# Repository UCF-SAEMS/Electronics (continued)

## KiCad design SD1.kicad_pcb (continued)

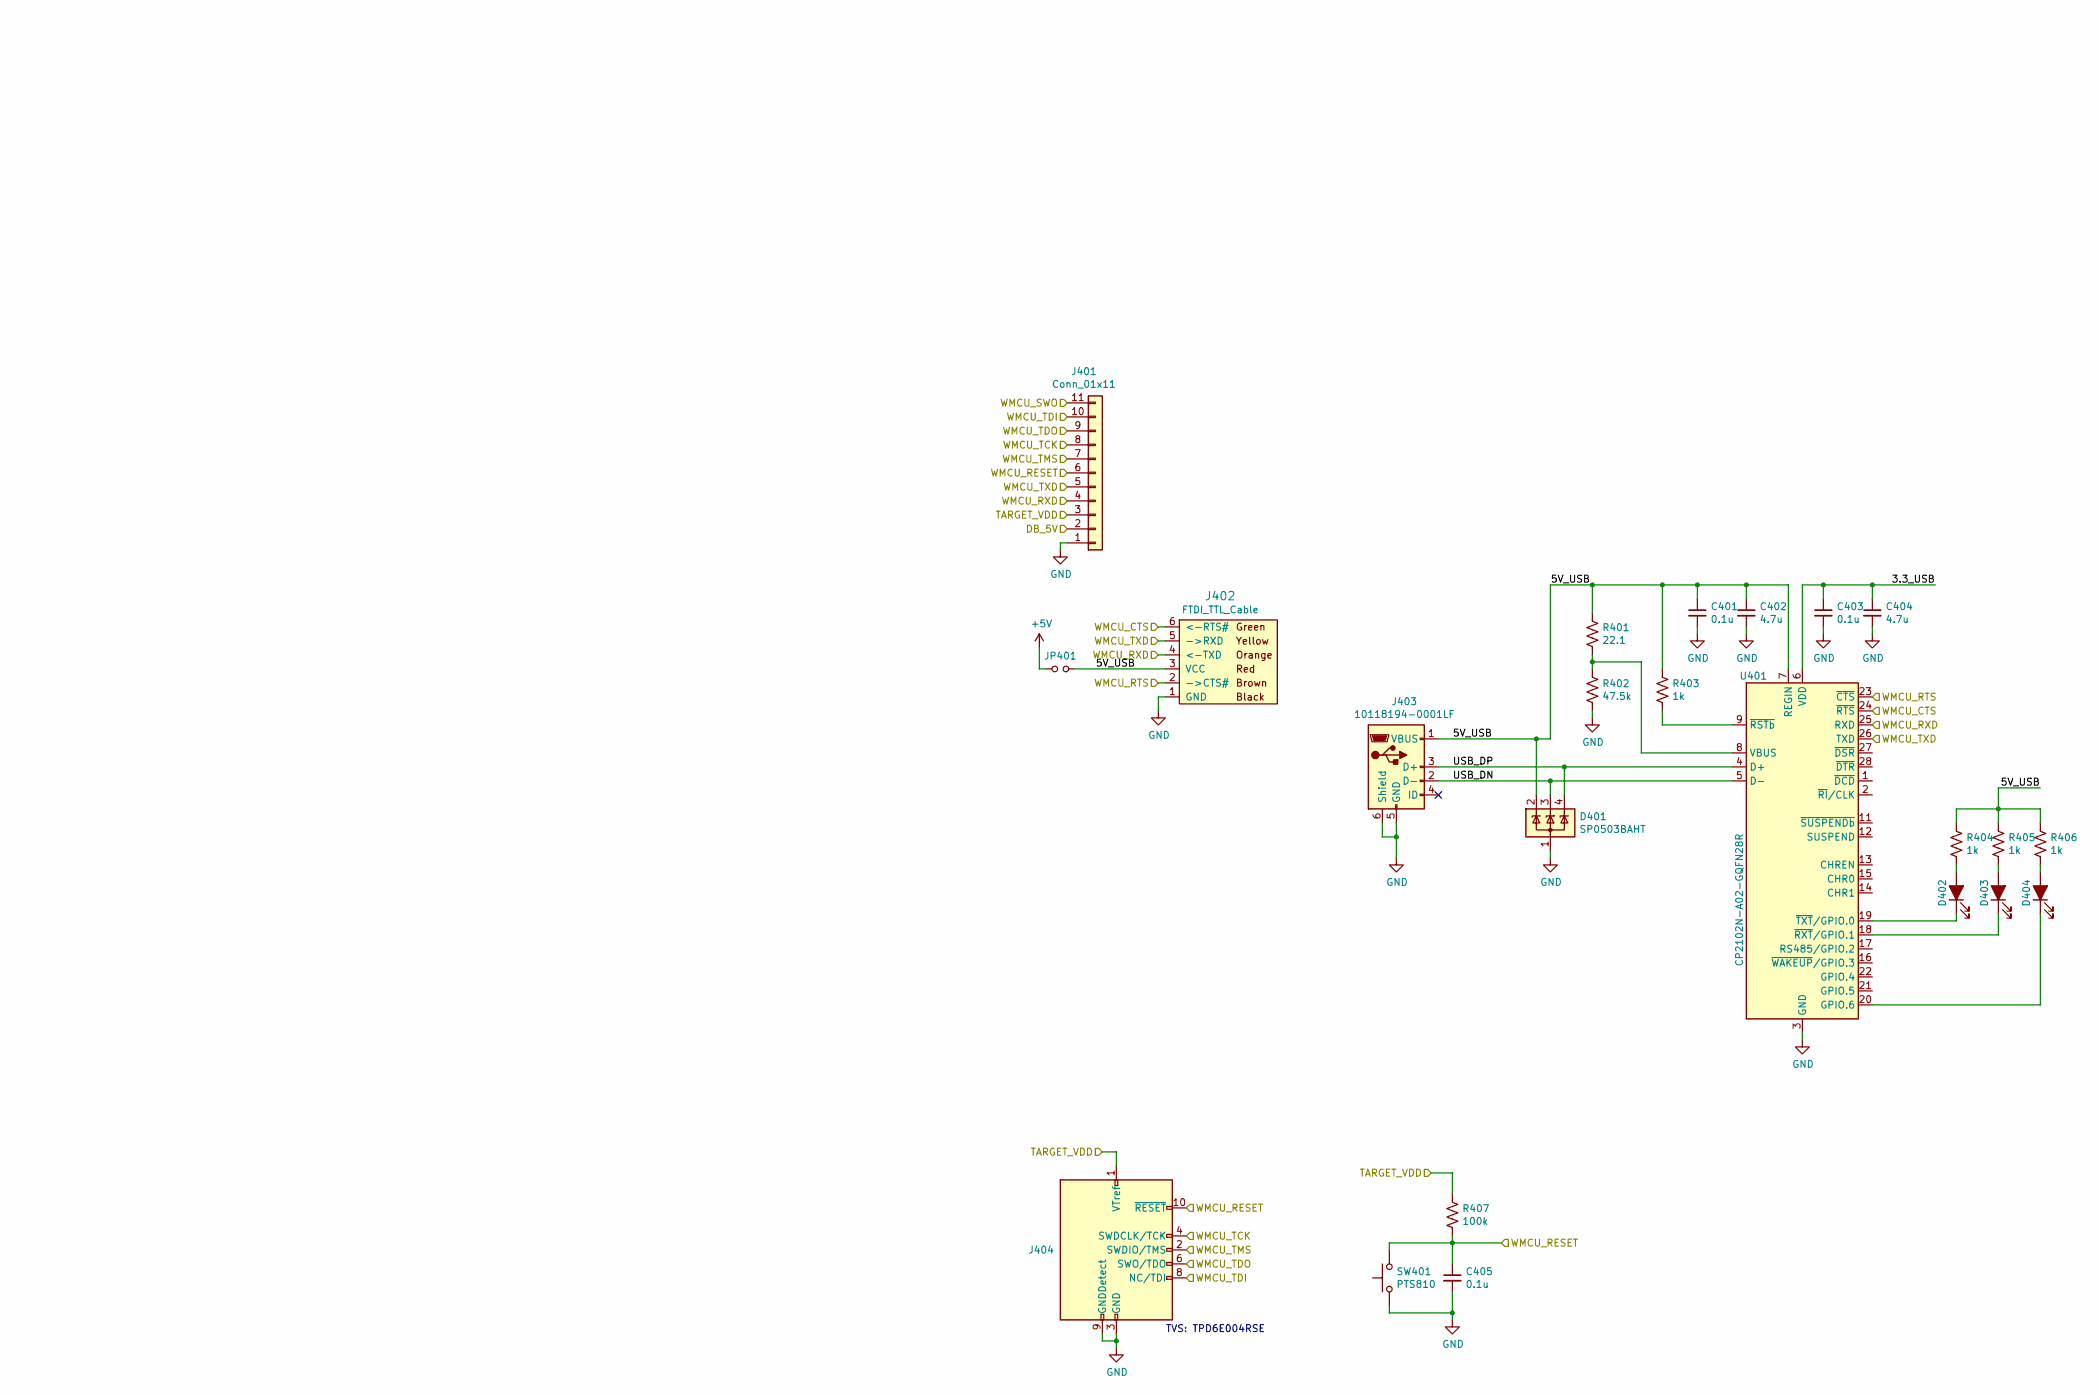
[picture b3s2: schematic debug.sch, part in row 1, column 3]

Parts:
C401, C403, C405: 0.1u; C_0603_1608Metric; MPN 0603B104K500CT; Digikey 1292-1643-1-ND
C402, C404: 4.7u; C_0603_1608Metric; MPN C0603C475K9PACTU; Digikey 399-3482-1-ND
D401: SP0503BAHT; SOT-143; MPN SP0503BAHTG; Digikey F2715CT-ND
D402, D403, D404: LED_ALT; LED_0603_1608Metric; MPN 150060RS75000; Digikey 732-4978-1-ND
J401: Conn_01x11; Molex_SL_171971-0011_1x11_P2.54mm_Vertical
J402: FTDI_TTL_Cable; PinHeader_1x06_P2.54mm_Vertical; LCSC C190819
J403: 10118194-0001LF; USB_Micro-B_Amphenol_10118194_Horizontal; MPN 10118194-0001LF; Digikey 609-4618-1-ND
J404: Conn_ARM_JTAG_SWD_10; PinHeader_2x05_P1.27mm_Wide_Shrouded_Vertical_SMD; MPN FTSH-105-01-L-DV-K; Digikey SAM8799-ND
JP401: Jumper_NO_Small; PinHeader_1x02_P2.54mm_Vertical
R401: 22.1; R_0603_1608Metric; MPN RC0603FR-0722R1L; Digikey 311-22.1HRCT-ND
R402: 47.5k; R_0603_1608Metric; MPN RC0603FR-0747K5L; Digikey 311-47.5KHRCT-ND
R403, R404, R405, R406: 1k; R_0603_1608Metric; MPN RC0603FR-071KL; Digikey 311-1.00KHRCT-ND
R407: 100k; R_0603_1608Metric; MPN RC0603FR-07100KL; Digikey 311-100KHRCT-ND
SW401: PTS810; SW_SPST_PTS810; Digikey CKN10503CT-ND
U401: CP2102N-A02-GQFN28R; QFN-28-1EP_5x5mm_P0.5mm_EP3.35x3.35mm; MPN CP2102N-A02-GQFN28R; Digikey 336-5890-1-ND

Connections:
+5V: JP401.1; also elsewhere on the board
/DIO12_RXD: J401.4, J402.4 (<-TXD), U401.25 (RXD); also elsewhere on the board
/DIO13_TXD: J401.5, J402.5 (->RXD), U401.26 (TXD); also elsewhere on the board
/DIO16_TDO: J401.9, J404.6 (SWO/TDO); also elsewhere on the board
/DIO17_TDI: J401.10, J404.8 (NC/TDI); also elsewhere on the board
/Debug and Serial/3.3_USB: C403.1, C404.1, U401.6 (VDD)
/Debug and Serial/5V_USB: C401.1, C402.1, D401.2 (K), J402.3 (VCC), J403.1 (VBUS), JP401.2, R401.2, R403.2, R404.2, R405.2, R406.2, U401.7 (REGIN)
/Debug and Serial/USB_DN: D401.3 (K), J403.2 (D-), U401.5 (D-)
/Debug and Serial/USB_DP: D401.4 (K), J403.3 (D+), U401.4 (D+)
/Debug and Serial/WMCU_RTS: J402.2 (->CTS#), U401.23 (~CTS); also elsewhere on the board
/WMCU_CTS: J402.6 (<-RTS#), U401.24 (~RTS); also elsewhere on the board
/WMCU_RESET: C405.1, J401.6, J404.10 (~RESET~), R407.1, SW401.2; also elsewhere on the board
/WMCU_TCK: J401.8, J404.4 (SWDCLK/TCK); also elsewhere on the board
/WMCU_TMS: J401.7, J404.2 (SWDIO/TMS); also elsewhere on the board
GND: C401.2, C402.2, C403.2, C404.2, C405.2, D401.1 (A), J401.1, J402.1 (GND), J403.5 (GND), J403.6 (Shield), J404.3 (GND), J404.5 (GND), J404.9 (GNDDetect), R402.1, SW401.1, U401.3 (GND), U401.29 (GND); also elsewhere on the board
unnamed: D402.1 (K), U401.19 (~TXT~/GPIO.0)
unnamed: D402.2 (A), R404.1
unnamed: D403.1 (K), U401.18 (~RXT~/GPIO.1)
unnamed: D403.2 (A), R405.1
unnamed: D404.1 (K), U401.20 (GPIO.6)
unnamed: D404.2 (A), R406.1
unnamed: R401.1, R402.2, U401.8 (VBUS)
unnamed: R403.1, U401.9 (~RSTb)

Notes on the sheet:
TVS: TPD6E004RSE
SERCOM 0

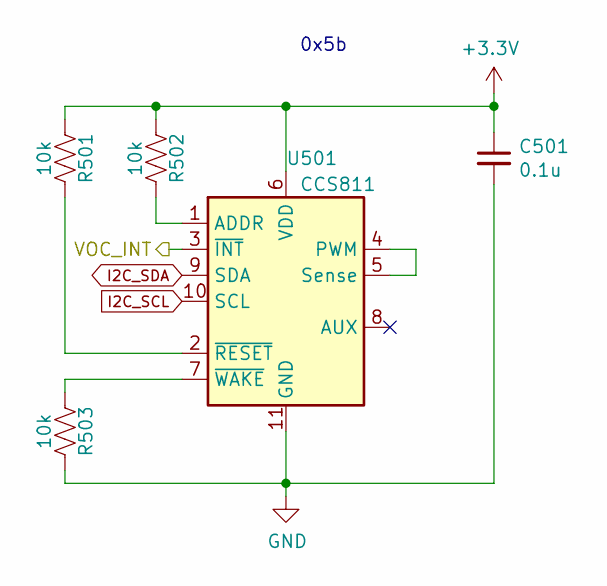
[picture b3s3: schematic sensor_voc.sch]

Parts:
C501: 0.1u; C_0603_1608Metric; MPN 0603B104K500CT; Digikey 1292-1643-1-ND
R501, R502, R503: 10k; R_0603_1608Metric; MPN RC0603FR-0710KL; Digikey 311-10.0KHRCT-ND
U501: CCS811; AMS_LGA-10-1EP_2.7x4mm_P0.6mm; MPN CCS811B-JOPR5K; Digikey CCS811B-JOPR5KCT-ND

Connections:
/VOC_INT: U501.3 (~INT); also elsewhere on the board
GND: C501.2, R503.2, U501.11 (GND); also elsewhere on the board
I2C_SCL: U501.10 (SCL); also elsewhere on the board
I2C_SDA: U501.9 (SDA); also elsewhere on the board
unnamed: R501.2, U501.2 (~RESET)
unnamed: R502.2, U501.1 (ADDR)
unnamed: R503.1, U501.7 (~WAKE)
unnamed: U501.4 (PWM), U501.5 (Sense)

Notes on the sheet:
0x5b

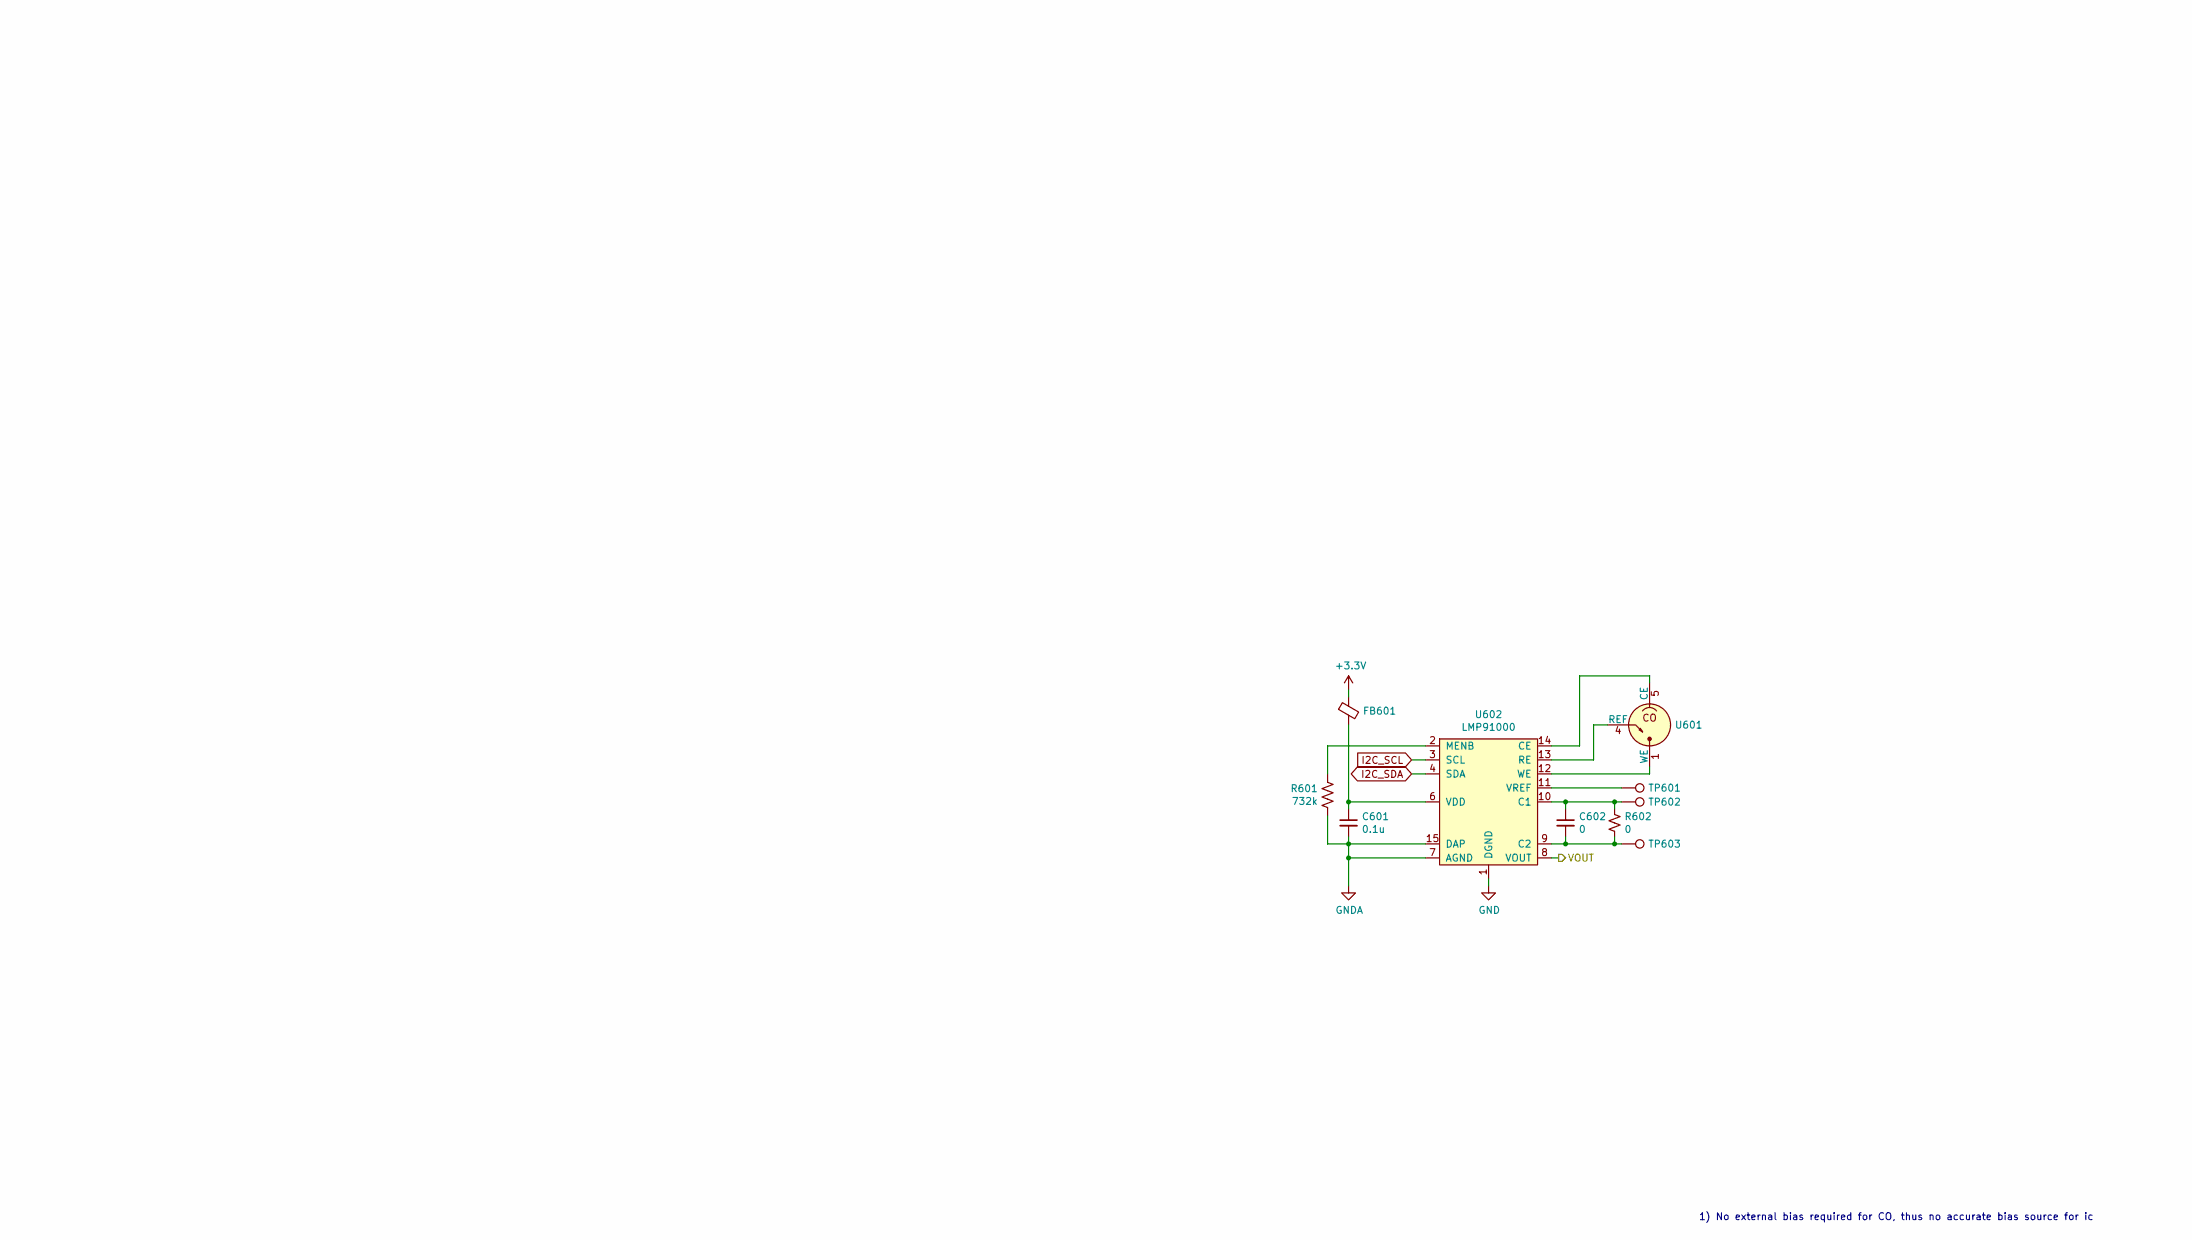
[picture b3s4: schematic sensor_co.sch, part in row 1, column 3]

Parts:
C601: 0.1u; C_0603_1608Metric; MPN 0603B104K500CT; Digikey 1292-1643-1-ND
C602: 0; C_0603_1608Metric
FB601: Ferrite_Bead_Small; L_0603_1608Metric; MPN BLM18PG471SN1D; Digikey 490-5223-1-ND
R601: 732k; R_0603_1608Metric; MPN RC0603FR-07732KL; Digikey 311-732KHRCT-ND
R602: 0; R_0603_1608Metric
TP601, TP602, TP603: TestPoint; TestPoint_Pad_D1.0mm
U601: 110-102; SPEC_110-102; MPN 110-102; Digikey 1684-1000-ND
U602: LMP91000; WSON-14-1EP_4.0x4.0mm_P0.5mm_EP2.6x2.6mm; MPN LMP91000SD; Digikey 296-44382-1-ND

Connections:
/CO_ADC: U602.8 (VOUT); also elsewhere on the board
GND: U602.1 (DGND); also elsewhere on the board
GNDA: C601.2, R601.2, U602.7 (AGND), U602.15 (DAP); also elsewhere on the board
I2C_SCL: U602.3 (SCL); also elsewhere on the board
I2C_SDA: U602.4 (SDA); also elsewhere on the board
unnamed: C601.1, FB601.2, U602.6 (VDD)
unnamed: C602.1, R602.1, TP602.1, U602.10 (C1)
unnamed: C602.2, R602.2, TP603.1, U602.9 (C2)
unnamed: R601.1, U602.2 (MENB)
unnamed: TP601.1, U602.11 (VREF)
unnamed: U601.1 (WE), U601.6 (WE), U602.12 (WE)
unnamed: U601.2 (NC), U601.3 (NC)
unnamed: U601.4 (REF), U602.13 (RE)
unnamed: U601.5 (CE), U602.14 (CE)

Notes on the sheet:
SERCOM 0
1) No external bias required for CO, thus no accurate bias source for ic

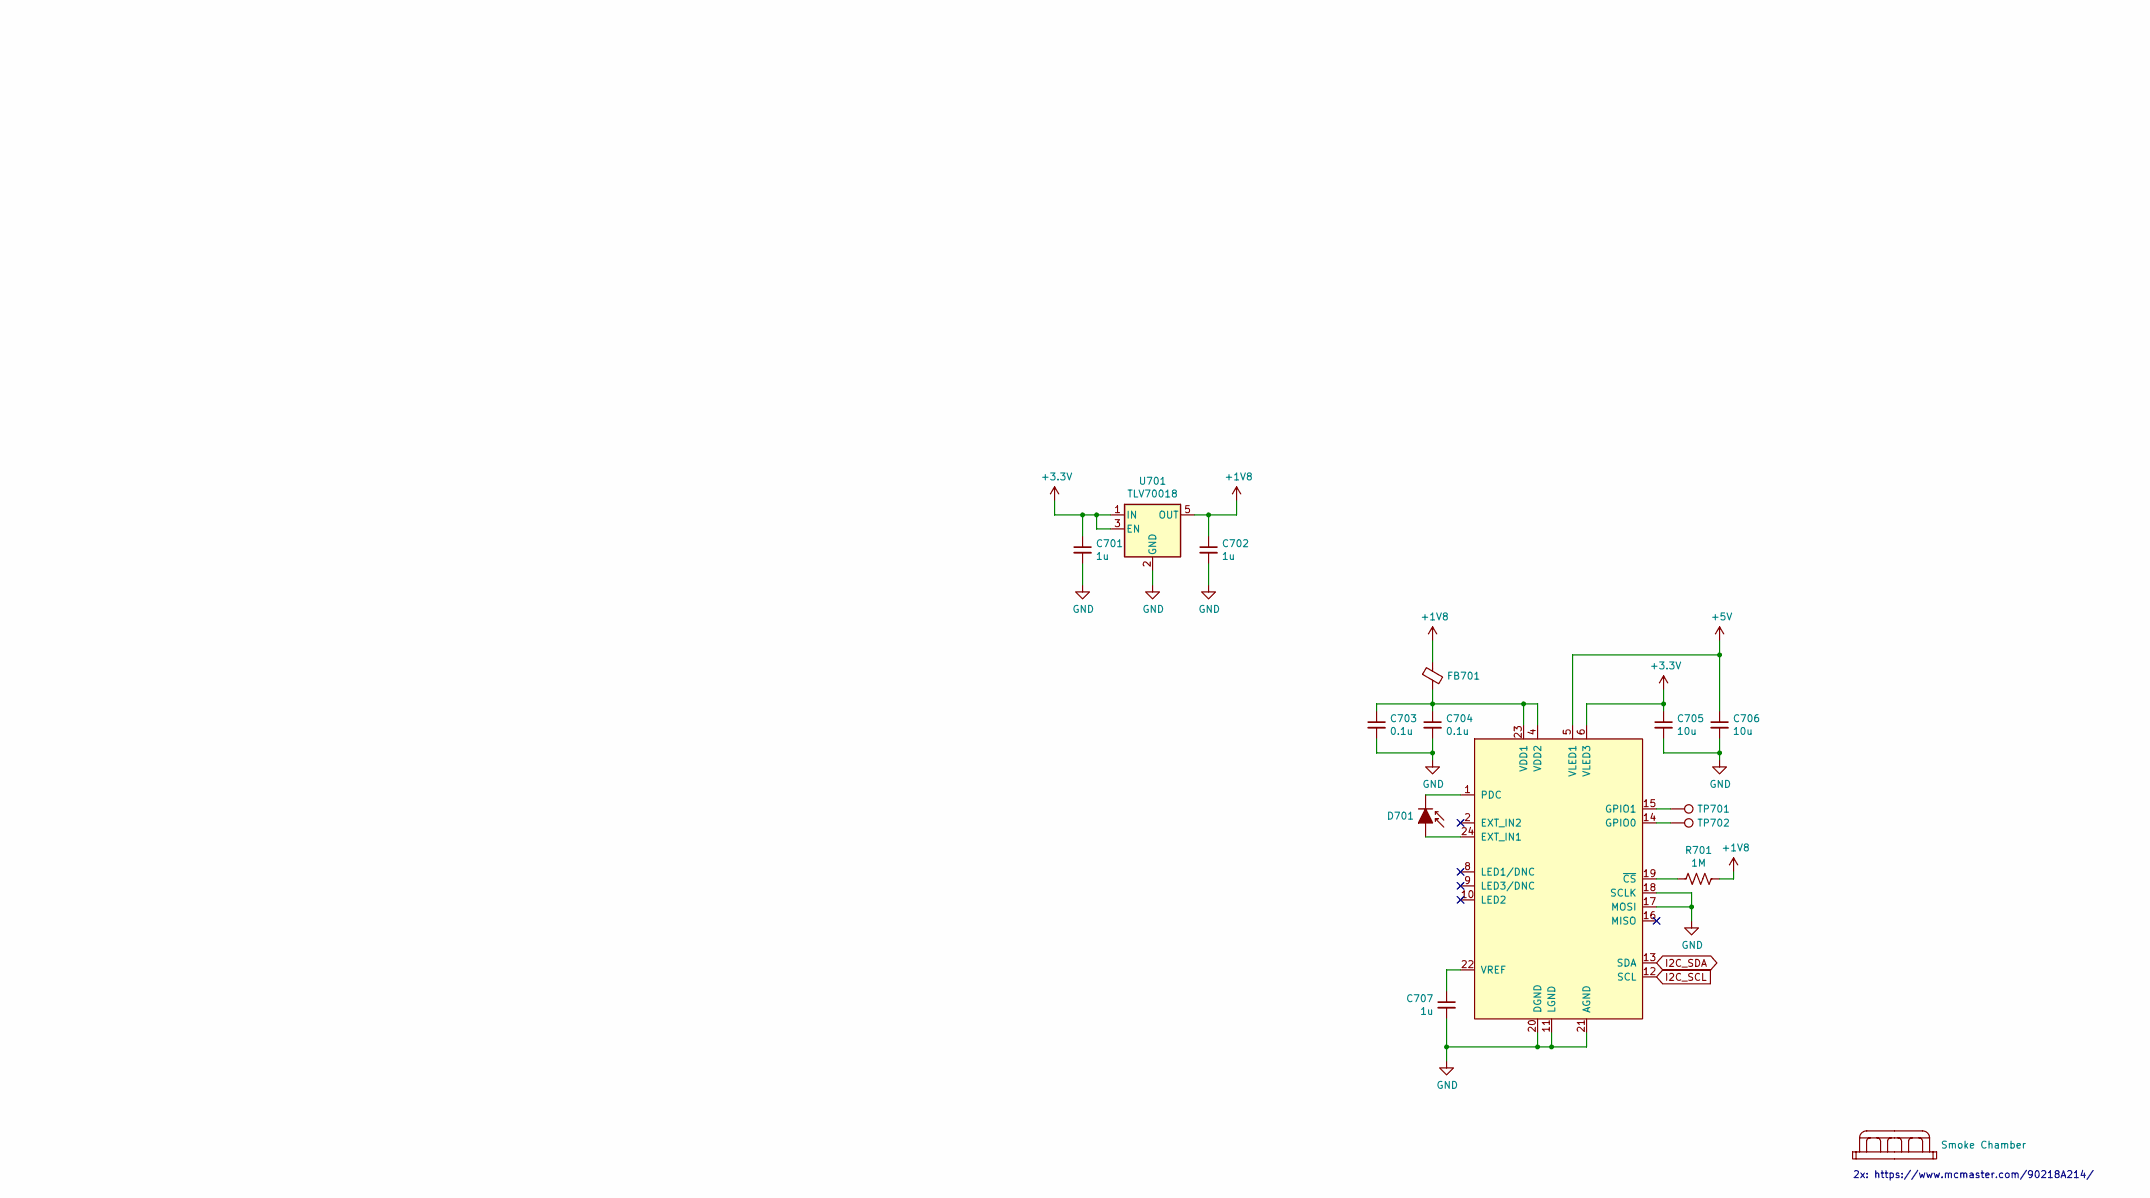
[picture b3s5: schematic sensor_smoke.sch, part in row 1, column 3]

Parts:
C701, C702, C707: 1u; C_0603_1608Metric; MPN TMK107B7105KA-T; Digikey 587-2984-1-ND
C703, C704: 0.1u; C_0603_1608Metric; MPN 0603B104K500CT; Digikey 1292-1643-1-ND
C705, C706: 10u; C_0603_1608Metric; MPN C1608X5R1A106M080AC; Digikey 445-6853-1-ND
D701: Photodiode alt; LED_D3.0mm_Clear; MPN PD204-6C; Digikey 1080-1140-ND
FB701: Ferrite_Bead_Small; L_0603_1608Metric; MPN BLM18PG471SN1D; Digikey 490-5223-1-ND
R701: 1M; R_0603_1608Metric; MPN RC0603FR-071ML; Digikey 311-1.00MHRCT-ND
TP701, TP702: TestPoint; TestPoint_Pad_D1.0mm
U701: TLV70018; SOT-353_SC-70-5; MPN TLV70018DCK; Digikey 296-32409-1-ND
U702: ADPD188BI; MPN ADPD188BI-ACEZR7; Digikey ADPD188BI-ACEZR7
U703: Smoke Chamber; ADPD188BI_Chamber

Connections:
+1V8: C702.1, FB701.1, R701.2, U701.5 (OUT)
+5V: C706.1, U702.5 (VLED1); also elsewhere on the board
GND: C701.2, C702.2, C703.2, C704.2, C705.2, C706.2, C707.2, U701.2 (GND), U701.4 (NC), U702.11 (LGND), U702.17 (MOSI), U702.18 (SCLK), U702.20 (DGND), U702.21 (AGND); also elsewhere on the board
I2C_SCL: U702.12 (SCL); also elsewhere on the board
I2C_SDA: U702.13 (SDA); also elsewhere on the board
unnamed: C703.1, C704.1, FB701.2, U702.4 (VDD2), U702.23 (VDD1)
unnamed: C707.1, U702.22 (VREF)
unnamed: D701.1 (K), U702.1 (PDC)
unnamed: D701.2 (A), U702.24 (EXT_IN1)
unnamed: R701.1, U702.19 (~CS)
unnamed: TP701.1, U702.15 (GPIO1)
unnamed: TP702.1, U702.14 (GPIO0)

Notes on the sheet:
SERCOM 0
2x: https://www.mcmaster.com/90218A214/

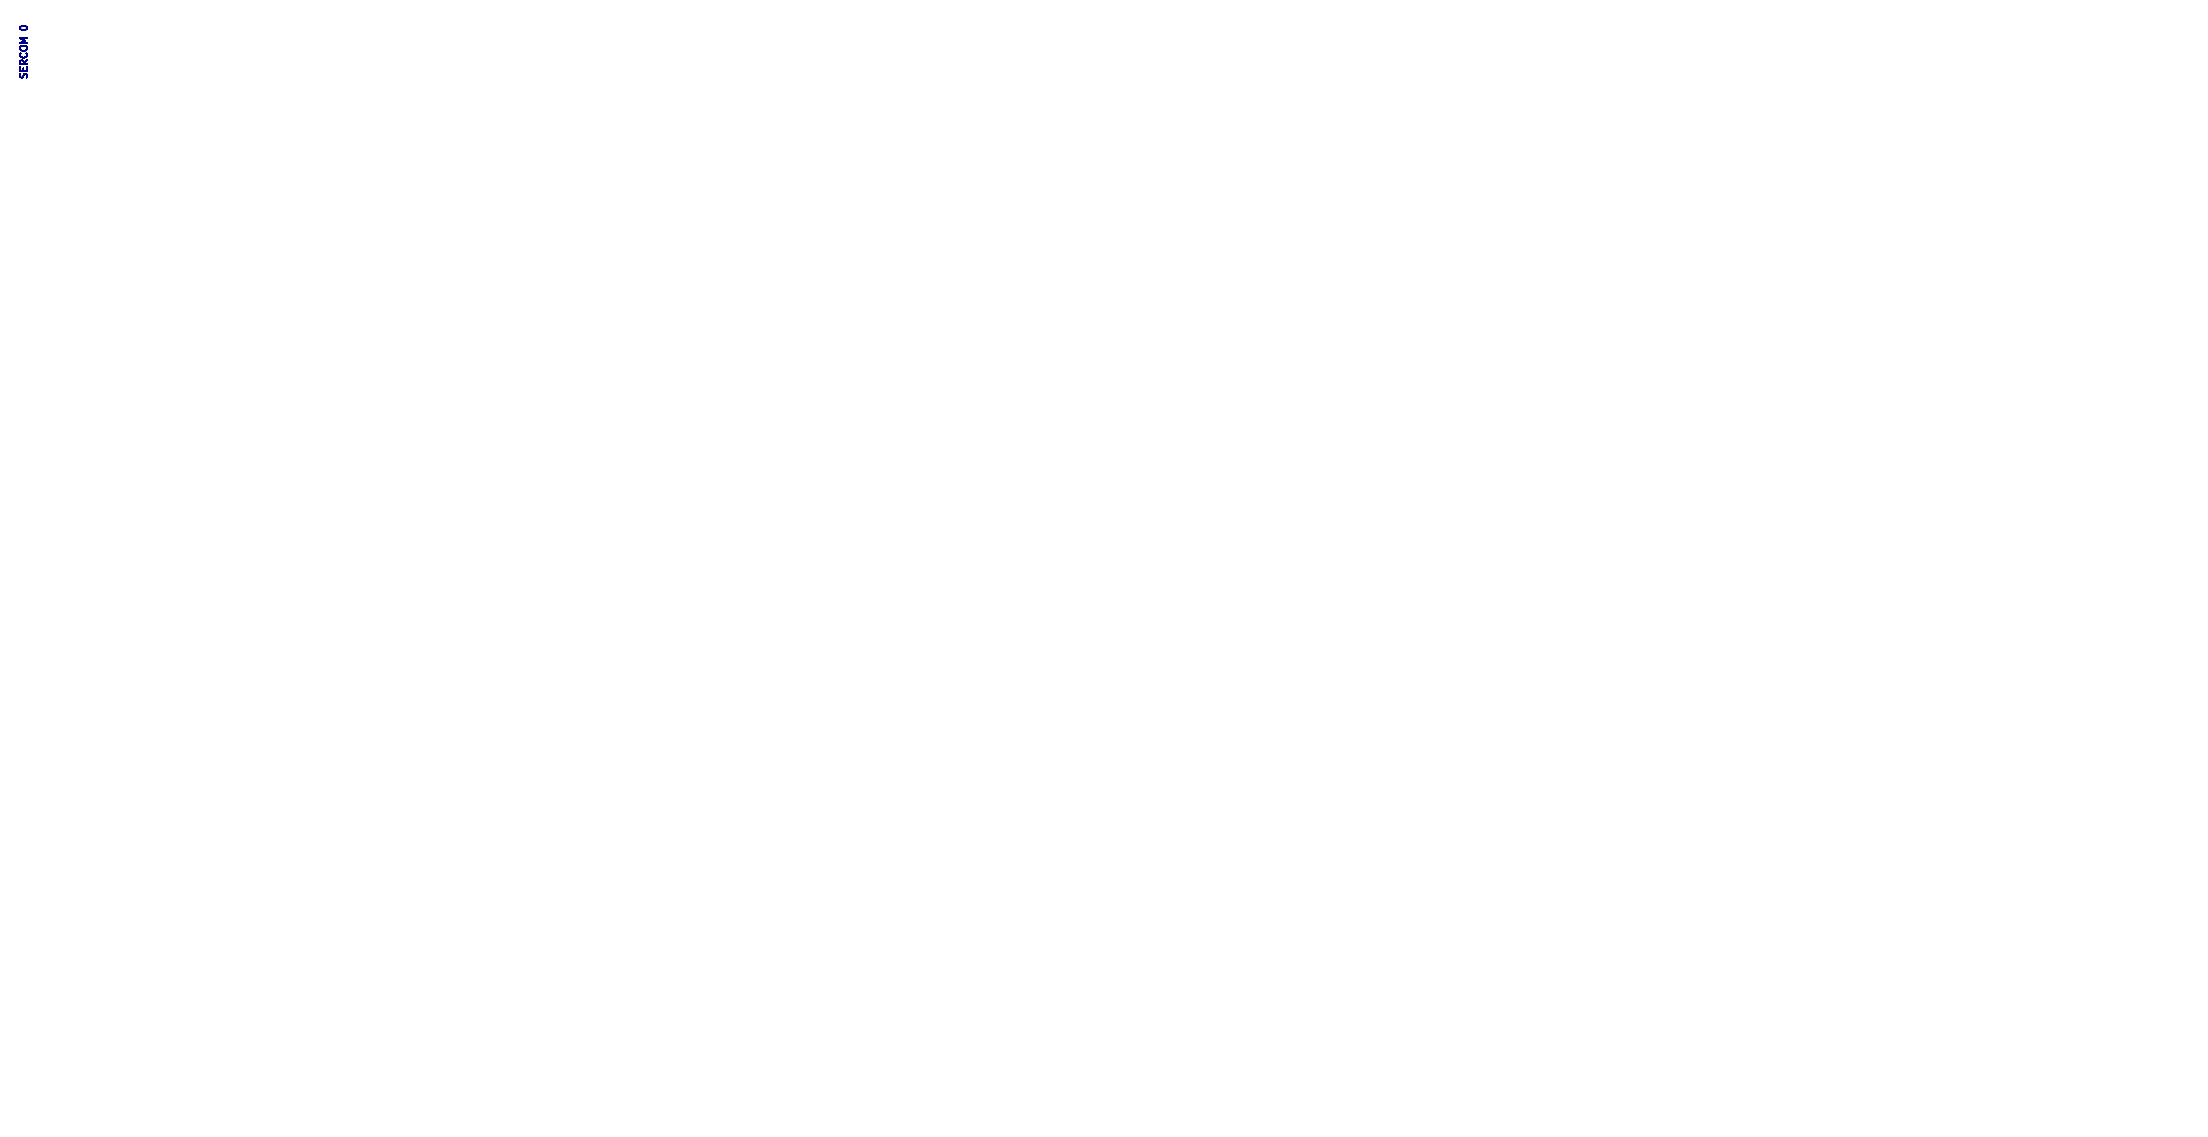
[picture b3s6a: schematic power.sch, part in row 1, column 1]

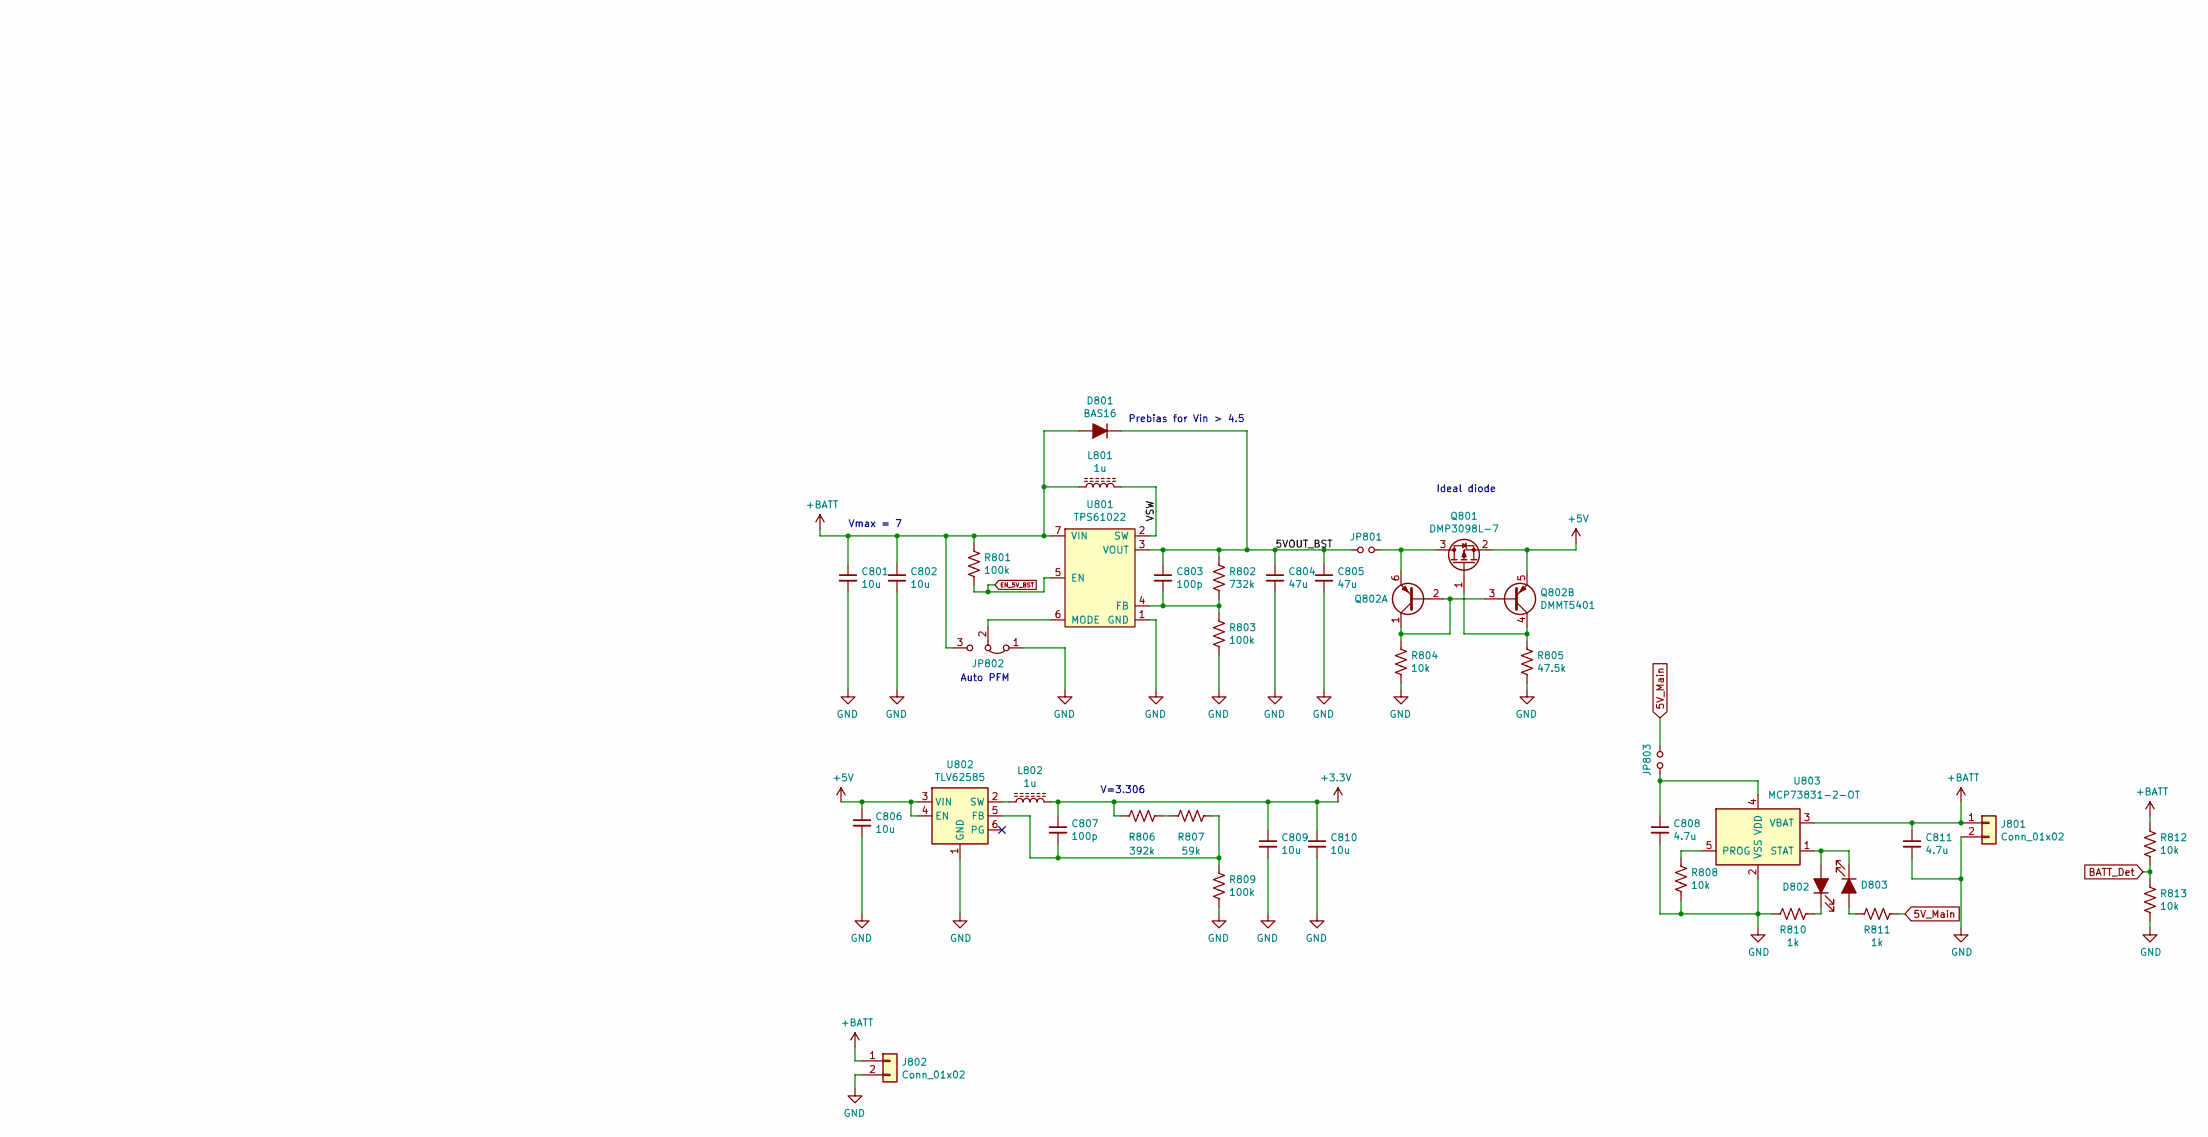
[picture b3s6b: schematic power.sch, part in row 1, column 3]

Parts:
C801, C802, C806, C809, C810: 10u; C_0603_1608Metric; MPN C1608X5R1A106M080AC; Digikey 445-6853-1-ND
C803, C807: 100p; C_0603_1608Metric; MPN CL10C101JC8NNNC; Digikey 1276-1295-1-ND
C804, C805: 47u; C_1210_3225Metric; Voltage 10V; MPN 1210X476K160CT; Digikey 587-5922-1-ND
C808, C811: 4.7u; C_0603_1608Metric; MPN C0603C475K9PACTU; Digikey 399-3482-1-ND
D801: BAS16; D_SOT-23_ANK; MPN BAS16-7-F; Digikey BAS16-FDICT-ND
D802, D803: LED_ALT; LED_0603_1608Metric; MPN 150060RS75000; Digikey 732-4978-1-ND
J801: Conn_01x02; JST_PH_B2B-PH-K_1x02_P2.00mm_Vertical; MPN B2B-PH-K-S(LF)(SN); Digikey B2B-PH-K-S(LF)(SN)
J802: Conn_01x02; PinHeader_1x02_P2.54mm_Vertical
JP801, JP803: Jumper_NO_Small; SolderJumper-2_P1.3mm_Open_TrianglePad1.0x1.5mm
JP802: Jumper_3_Bridged12; SolderJumper-3_P1.3mm_Bridged12_Pad1.0x1.5mm
L801, L802: 1u; L_Wuerth_HCI-5040; MPN 744316100; Digikey 732-6176-1-ND
Q801: DMP3098L-7; SOT-23-6; MPN DMP3098L-7; Digikey DMP3098LDICT-ND
Q802: DMMT5401; SOT-23-6; MPN DMMT5401-7-F; Digikey DMMT5401-FDICT-ND
R801, R803, R809: 100k; R_0603_1608Metric; MPN RC0603FR-07100KL; Digikey 311-100KHRCT-ND
R802: 732k; R_0603_1608Metric; MPN RC0603FR-07732KL; Digikey 311-732KHRCT-ND
R804, R808, R812, R813: 10k; R_0603_1608Metric; MPN RC0603FR-0710KL; Digikey 311-10.0KHRCT-ND
R805: 47.5k; R_0603_1608Metric; MPN RC0603FR-0747K5L; Digikey 311-47.5KHRCT-ND
R806: 392k; R_0603_1608Metric; MPN RC0603FR-07392KL; Digikey 311-392KHRCT-ND
R807: 59k; R_0603_1608Metric; MPN RC0603FR-0759KL; Digikey 311-59.0KHRCT-ND
R810, R811: 1k; R_0603_1608Metric; MPN RC0603FR-071KL; Digikey 311-1.00KHRCT-ND
U801: TPS61022; Texas_VQFN-HR-7; MPN TPS61022; Digikey 296-TPS61022RWURCT-ND
U802: TLV62585; SOT-563; MPN TLV62585DRLR; Digikey 296-51694-1-ND
U803: MCP73831-2-OT; SOT-23-5; MPN MCP73831T-2ACI/OT; Digikey MCP73831T-2ACI/OTCT-ND

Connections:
5V_Main: JP803.2, R811.2; also elsewhere on the board
+5V: C806.1, Q801.2 (S), Q802.5 (E2), U802.3 (VIN), U802.4 (EN); also elsewhere on the board
+BATT: C801.1, C802.1, C811.1, D801.2 (A), J801.1, J802.1, JP802.3 (B), L801.1, R801.2, R812.1, U801.7 (VIN), U803.3 (VBAT)
/Power/5VOUT_BST: C803.1, C804.1, C805.1, D801.1 (K), JP801.1, R802.2, U801.3 (VOUT)
/Power/VSW: L801.2, U801.2 (SW)
BATT_Det: R812.2, R813.1; also elsewhere on the board
EN_5V_BST: R801.1, U801.5 (EN); also elsewhere on the board
GND: C801.2, C802.2, C804.2, C805.2, C806.2, C808.2, C809.2, C810.2, C811.2, J801.2, J802.2, JP802.1 (A), R803.1, R804.2, R805.1, R808.2, R809.1, R810.1, R813.2, U801.1 (GND), U802.1 (GND), U803.2 (VSS); also elsewhere on the board
unnamed: C803.2, R802.1, R803.2, U801.4 (FB)
unnamed: C807.2, R807.2, R809.2, U802.5 (FB)
unnamed: C808.1, JP803.1, U803.4 (VDD)
unnamed: D802.1 (K), R810.2
unnamed: D802.2 (A), D803.1 (K), U803.1 (STAT)
unnamed: D803.2 (A), R811.1
unnamed: JP801.2, Q801.3 (D), Q802.6 (E1)
unnamed: JP802.2 (C), U801.6 (MODE)
unnamed: L802.1, U802.2 (SW)
unnamed: Q801.1 (G), Q802.4 (C2), R805.2
unnamed: Q802.1 (C1), Q802.2 (B1), Q802.3 (B2), R804.1
unnamed: R806.2, R807.1
unnamed: R808.1, U803.5 (PROG)

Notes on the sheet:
SERCOM 0
Vmax = 7
Prebias for Vin > 4.5
Auto PFM
V=3.306
Ideal diode
